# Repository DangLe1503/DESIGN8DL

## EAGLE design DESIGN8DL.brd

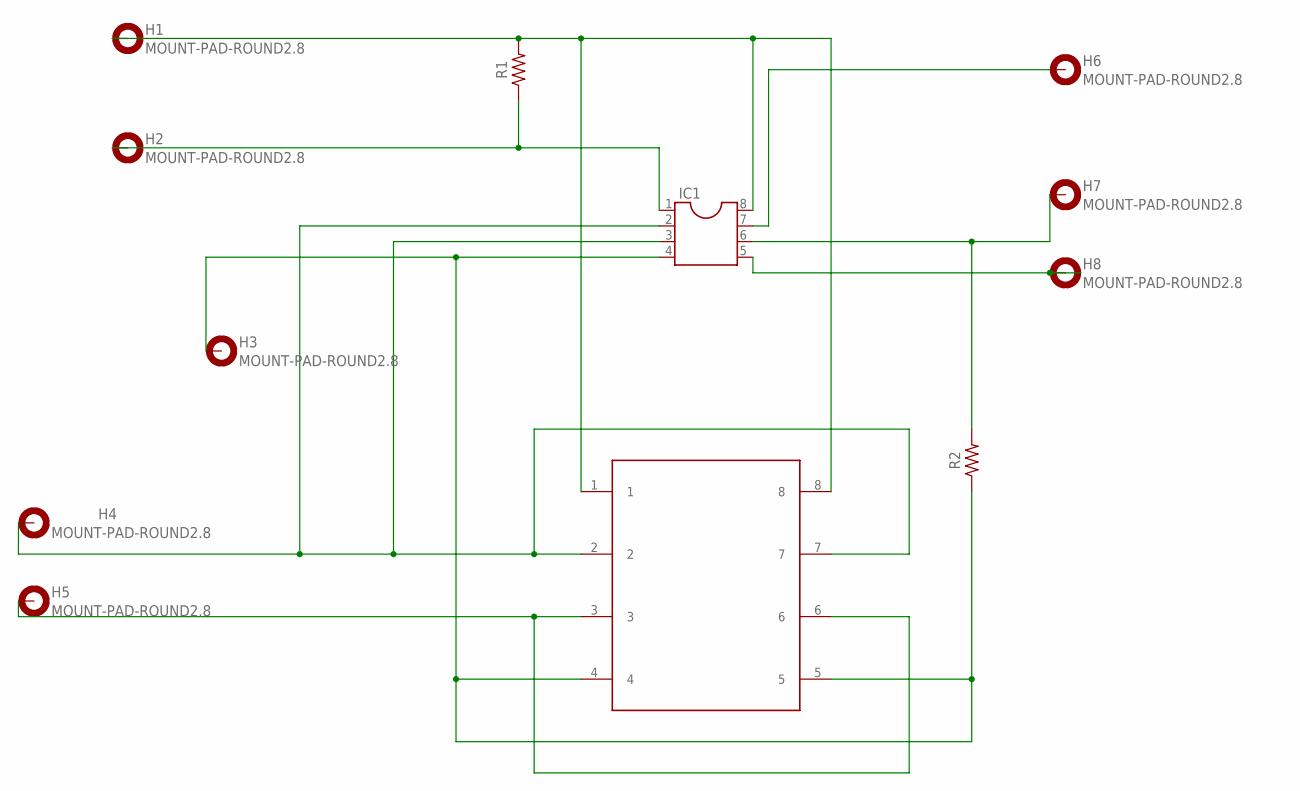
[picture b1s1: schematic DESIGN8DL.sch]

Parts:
H1, H2, H3, H4, H5, H6, H7, H8: MOUNT-PAD-ROUND2.8; 2,8-PAD
IC1: DIL8; DIL08
R1, R2: R-US_AXIAL-7.2MM-PITCH; RESAD724W46L381D178B
U$4: JOYPAD

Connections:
unnamed: H1.B2,8, IC1.8, R1.2, U$4.1, U$4.8
unnamed: H2.B2,8, IC1.1, R1.1
unnamed: H6.B2,8, IC1.7
unnamed: H7.B2,8, IC1.6, R2.2
unnamed: H8.B2,8, IC1.5
unnamed: H4.B2,8, IC1.2, IC1.3, U$4.2, U$4.7
unnamed: H5.B2,8, U$4.3, U$4.6
unnamed: H3.B2,8, IC1.4, R2.1, U$4.4, U$4.5

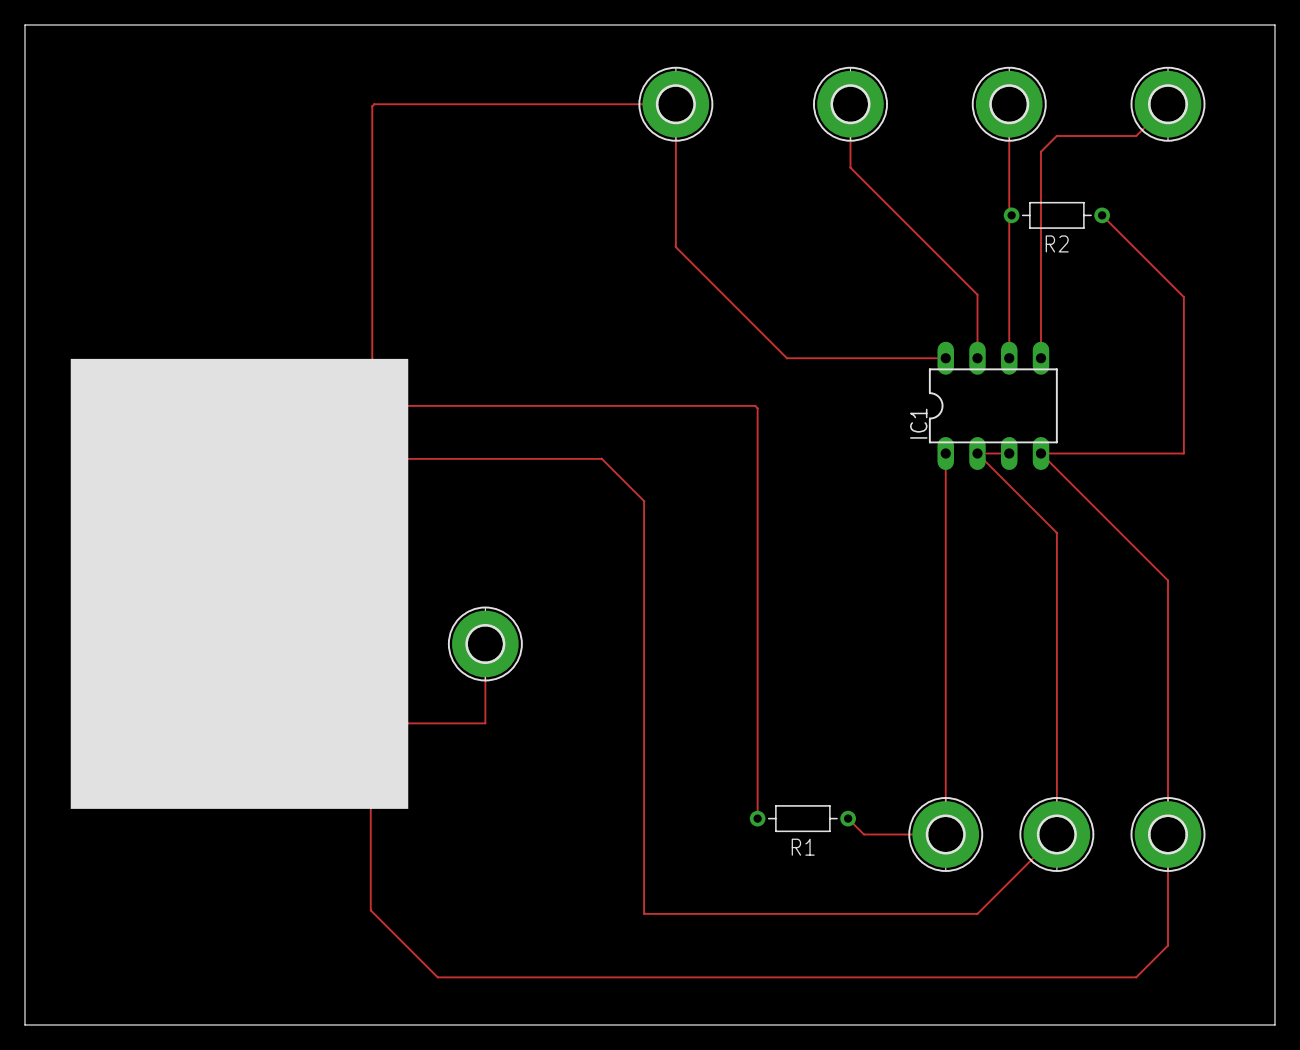
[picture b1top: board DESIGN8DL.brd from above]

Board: 2 copper layers, 100.0 x 80.0 mm, 12 parts (0 on the bottom side), 8 nets.
